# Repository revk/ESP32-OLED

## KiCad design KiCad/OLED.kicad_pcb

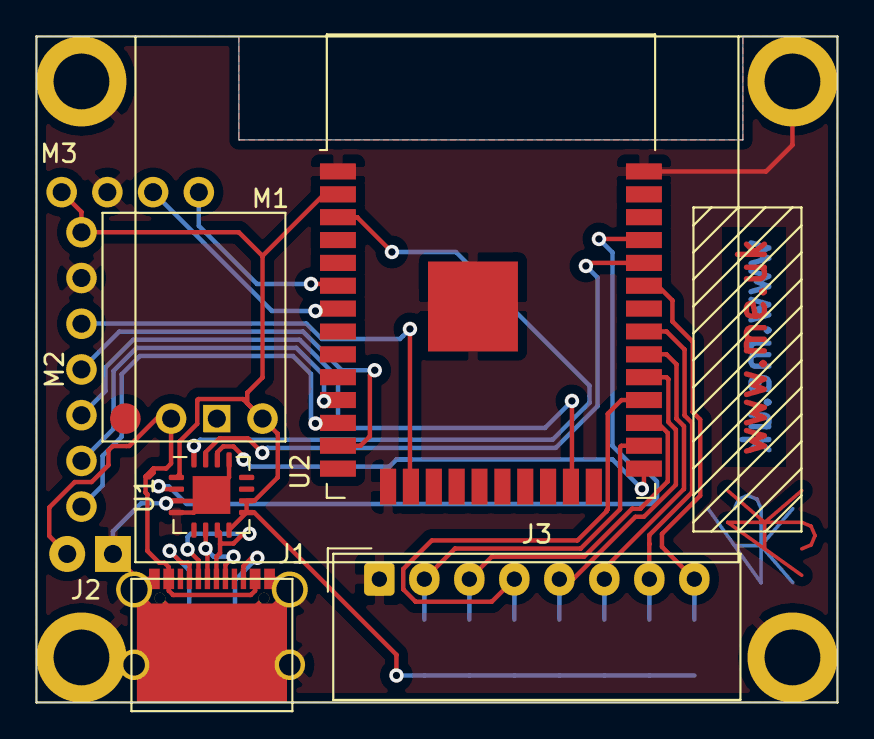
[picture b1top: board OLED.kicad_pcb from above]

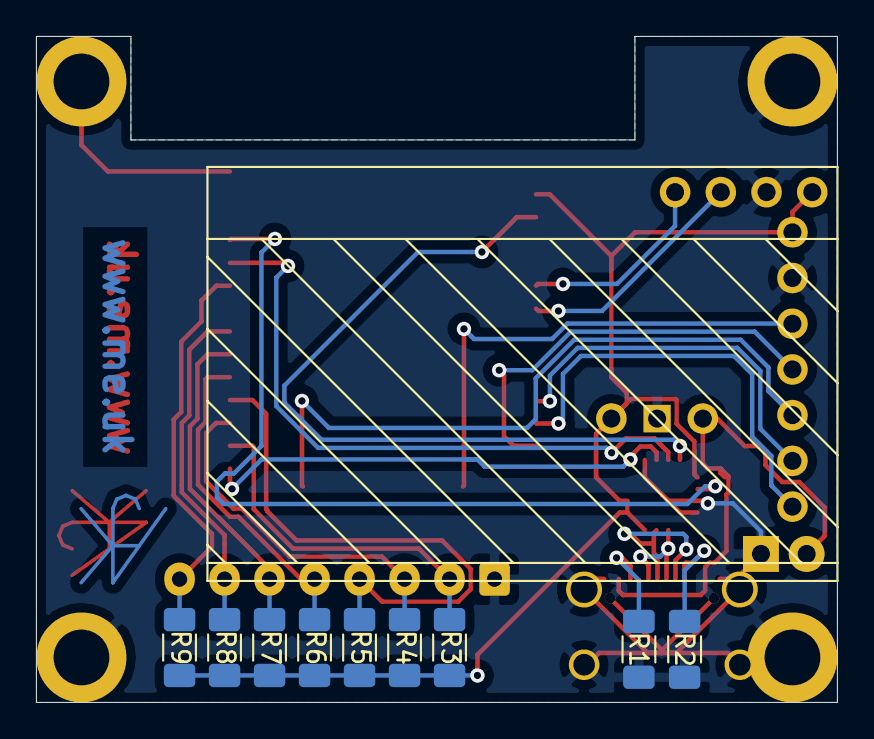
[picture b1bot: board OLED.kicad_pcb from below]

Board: 2 copper layers, 44.5 x 37.0 mm, 17 parts (10 on the bottom side), 25 nets.

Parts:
J1: USB-C; USC16-TR-Round
J2: DC
J3: GPIO; Molex_SPOX_5268-08A_1x08_P2.50mm_Horizontal
M1: D24V5F3-NoSHDN
M2: OLED1.5-RGB
M3: SCD30-4pin
R1, R2: 5K1; R_1206_3216Metric_Pad1.30x1.75mm_HandSolder
R3, R4, R5, R6, R7, R8, R9: NF; R_1206_3216Metric_Pad1.30x1.75mm_HandSolder
U1: FT230XQ; QFN-16-1EP_4x4mm_P0.65mm_EP2.1x2.1mm
U2: ESP32-WROOM-32

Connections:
+3V3: M1.4, M2.1, M3.1, R3.2, R4.2, R5.2, R6.2, R7.2, R8.2, R9.2, U1.1, U1.8, U1.9, U1.10, U2.2
CO2-SCL: M3.3, U2.7
CO2-SDA: M3.4, U2.6
GND: J1.A1, J1.A12, J1.B1, J1.B12, J1.S1, J2.1, J3.1, M1.3, M2.2, M2.S, M3.2, R1.2, R2.2, U1.3, U1.4, U1.13, U1.17, U2.1, U2.15, U2.38, U2.39
IO1: J3.2, R3.1, U2.26
IO2: J3.3, R4.1, U2.27
IO3: J3.4, R5.1, U2.28
IO4: J3.5, R6.1, U2.29
IO5: J3.6, R7.1, U2.30
IO6: J3.7, R8.1, U2.31
IO7: J3.8, R9.1, U2.33
unnamed: J1.A4, J1.A9, J1.B4, J1.B9, J2.2, M1.2
unnamed: J1.A5, R2.1
unnamed: J1.A6, J1.B6, U1.6
unnamed: J1.A7, J1.B7, U1.7
unnamed: J1.B5, R1.1
unnamed: U1.2, U2.35
unnamed: U1.14, U2.25
unnamed: U1.15, U2.34
unnamed: U1.16, U2.3
OLED-CS0: M2.5, U2.23
OLED-DC: M2.6, U2.11
OLED-MOSI: M2.3, U2.16
OLED-RST: M2.7, U2.12
OLED-SCLK: M2.4, U2.13

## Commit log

2019-09-19 Started on OLED code
2019-09-19 More code
2019-09-19 Added flip
2019-09-19 Font tinkering
2019-09-19 D'Oh
2019-09-19 Bug fix
2019-09-20 Tidy
2019-09-20 Silly mistake
2019-09-20 font0 tweaks
2019-09-20 Handle non display
2019-09-21 Tweak
2019-09-21 Try that
2019-09-21 Mutex
2019-10-22 Pixel
2019-10-22 Ooops
2019-10-23 Format
2019-10-25 Tweak to get pixel
2019-11-01 oled space from malloc
2019-11-01 Bugs
2019-11-17 Tweak failure
2019-11-17 Typo
2019-11-17 Mutex calls
2019-11-17 Ah, re-reading, we were fine
2021-03-09 New directory
2021-03-09 New PCB
2021-03-09 Tracked
2021-03-09 Plotted
